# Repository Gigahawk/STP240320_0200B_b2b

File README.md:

# STP240320_0200B_b2b

A PCB that adapts the ribbon connector of the STP240320_0200B_b2b to a [Molex SlimStack 55560-0168](https://www.molex.com/molex/products/part-detail/pcb_headers/0555600168)
> The footprint used is the KiCad native [55560-0161](https://gitlab.com/kicad/libraries/kicad-footprints/-/blob/master/Connector_Molex.pretty/Molex_SlimStack_55560-0161_2x08_P0.50mm_Vertical.kicad_mod), there doesn't seem to be an appreciable difference.

## Background

The STP240320_0200B is a 2.0" 240x320 ST7789 based TFT display.
It is used in many 2.0" ST7789 display modules, some examples:
- [Adafruit 2.0" 320x240 Color IPS TFT Display with microSD Card Breakout](https://www.adafruit.com/product/4311)
- [Waveshare 240×320, General 2inch IPS LCD Display Module](https://www.waveshare.com/2inch-lcd-module.htm)

The display itself can be purchased from [Surenoo Display on AliExpress](https://www.aliexpress.com/item/4000469644849.html), if you find other vendors please feel free to open an issue or PR.

The flex ribbon connector isn't designed to go into a FFC connector, so this board is used to connectorize the display.

### Update 2022-10-27
I have recently purchased more of these displays and they are not the same as the displays I originally purchased back in 2020, nor do they match the picture in the listing.

Original is on the left, the display I recently received on the right:

While I have not tested this new display with the adapter, visually they appear to be functionally identical.
The display housing has the exact same outer dimensions.
The connector has the same number of pins with the same pitch and in the same order.
The connector location relative to the display housing appears to be the same as well

Since I have not tested the display yet with the breakout, I do not know whether:
- The pinout of the connector is actually identical to the original
- The viewing area location matches the original display

## STP240320_0200B_b2b

The `STP240320_0200B_b2b` folder contains KiCad files for the board to board adapter shown above

## STP240320_0200B_b2b_breakout

The `STP240320_0200B_b2b_breakout` folder contains KiCad files for a breakout board similar to the Adafruit breakout with a matching [Molex SlimStack 54722-0164](https://www.molex.com/molex/products/part-detail/pcb_receptacles/0547220164).

## Notes

There appear to be similar displays with SPI interfaces that have FPCs suitable for direct connection into an FFC connector.

The STP240320_0200A sold from the same link above is listed as an 8-bit parallel interface only, but the display looks suspiciously close to some other listings on AliExpress:
- https://www.aliexpress.com/i/1005003204020216.html
- https://www.aliexpress.com/i/2045504893.html

These listings list pins 3 and 4 as `IM1` and `IM2`, which can be used to set the display mode to 8-bit parallel or SPI.

[LCD Wiki](http://www.lcdwiki.com/2.0inch_IPS_Module) documents a breakout board using this display, with a [schematic](http://www.lcdwiki.com/res/MSP2008/2.0IPS_MSP2008_Schematic.pdf) showing the `IMx` pins configuring the display for SPI operation.
The schematic has a link to http://www.qdtft.com, but they don't seem to list this module anymore.

There are a few vendors on AliExpress that appear to be selling this breakout:
- https://www.aliexpress.com/i/1005004116872380.html
- https://www.aliexpress.com/i/1005004116832438.html
- https://www.aliexpress.com/i/32705031396.html
- https://www.aliexpress.com/i/1005004116821841.html

### Update 2022-11-05

I've purchased breakouts from the first link in the above list (XunMing Store), some notes about them:
- They work identically to the STP240320_0200B
    - Tested using Adafruit's [CircuitPython Displayio Quickstart Guide](https://learn.adafruit.com/2-0-inch-320-x-240-color-ips-tft-display/circuitpython-displayio-quickstart)
- The breakout boards use a rather strong foam tape that makes the display hard to separate from the PCB, if possible I recommend purchasing the bare display module on its own for integration into other projects, and to use the breakout only for prototyping
- The display module is significantly larger in all dimensions compared to the STP240320_0200B
    - The bezels are significantly larger, and the whole module is thicker
- The FFC connector used does not save any space compared to the SlimStack connector used.
    - When fully assembled (i.e. B2B adapter connected to the breakout), the SlimStack connectors are about the same height as the closed FFC connector
    - The FFC connector is significantly wider than both the SlimStack connector and the B2B adapter board (perpendicular to the direction of FFC insertion)
    - The FFC connector is about the same length of the B2B adapter board (parallel to the direction of FFC insertion)

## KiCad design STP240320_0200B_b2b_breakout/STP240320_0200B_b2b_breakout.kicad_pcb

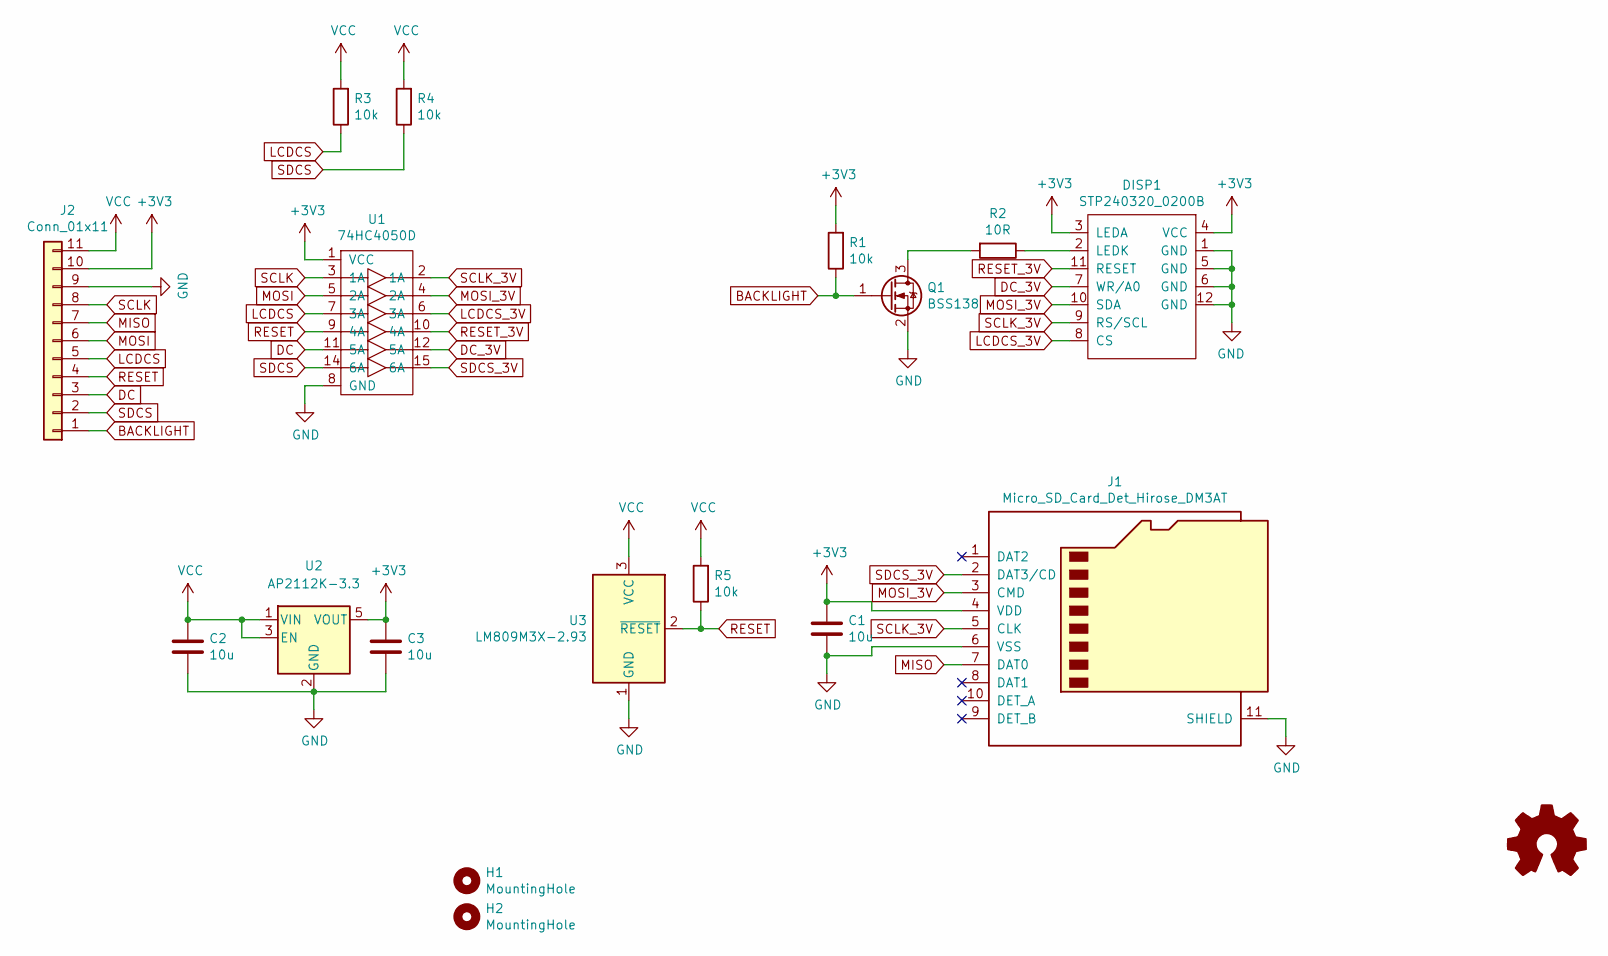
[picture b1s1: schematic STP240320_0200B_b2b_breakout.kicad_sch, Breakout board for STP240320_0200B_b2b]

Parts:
C1, C2, C3: 10u; C_0805_2012Metric_Pad1.18x1.45mm_HandSolder
DISP1: STP240320_0200B; Molex_SlimStack_54722-0164_2x08_P0.50mm_Vertical
H1, H2: MountingHole; MountingHole_2.5mm_Pad
J1: Micro_SD_Card_Det_Hirose_DM3AT; microSD_HC_Hirose_DM3AT-SF-PEJM5
J2: Conn_01x11; PinHeader_1x11_P2.54mm_Vertical
LOGO1: Logo_Open_Hardware_Small; OSHW-Logo2_9.8x8mm_Mask
Q1: BSS138; SOT-23
R1, R3, R4, R5: 10k; R_0805_2012Metric_Pad1.20x1.40mm_HandSolder
R2: 10R; R_0805_2012Metric_Pad1.20x1.40mm_HandSolder
U1: 74HC4050D; SOIC-16_3.9x9.9mm_P1.27mm
U2: AP2112K-3.3; SOT-23-5
U3: LM809M3X-2.93; SOT-23

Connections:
+3V3: C1.1, C3.1, DISP1.3 (LEDA), DISP1.4 (VCC), J1.4 (VDD), J2.10, R1.2, U1.1 (VCC), U2.5 (VOUT)
BACKLIGHT: J2.1, Q1.1 (G), R1.1
DC: J2.3, U1.11 (5A)
DC_3V: DISP1.7 (WR/A0), U1.12 (5A)
GND: C1.2, C2.2, C3.2, DISP1.1 (GND), DISP1.5 (GND), DISP1.6 (GND), DISP1.12 (GND), J1.6 (VSS), J1.11 (SHIELD), J2.9, Q1.2 (S), U1.8 (GND), U2.2 (GND), U3.1 (GND)
LCDCS: J2.5, R3.1, U1.7 (3A)
LCDCS_3V: DISP1.8 (CS), U1.6 (3A)
MISO: J1.7 (DAT0), J2.7
MOSI: J2.6, U1.5 (2A)
MOSI_3V: DISP1.10 (SDA), J1.3 (CMD), U1.4 (2A)
unnamed: DISP1.2 (LEDK), R2.1
unnamed: Q1.3 (D), R2.2
RESET: J2.4, R5.1, U1.9 (4A), U3.2 (~RESET)
RESET_3V: DISP1.11 (RESET), U1.10 (4A)
SCLK: J2.8, U1.3 (1A)
SCLK_3V: DISP1.9 (RS/SCL), J1.5 (CLK), U1.2 (1A)
SDCS: J2.2, R4.1, U1.14 (6A)
SDCS_3V: J1.2 (DAT3/CD), U1.15 (6A)
VCC: C2.1, J2.11, R3.2, R4.2, R5.2, U2.1 (VIN), U2.3 (EN), U3.3 (VCC)

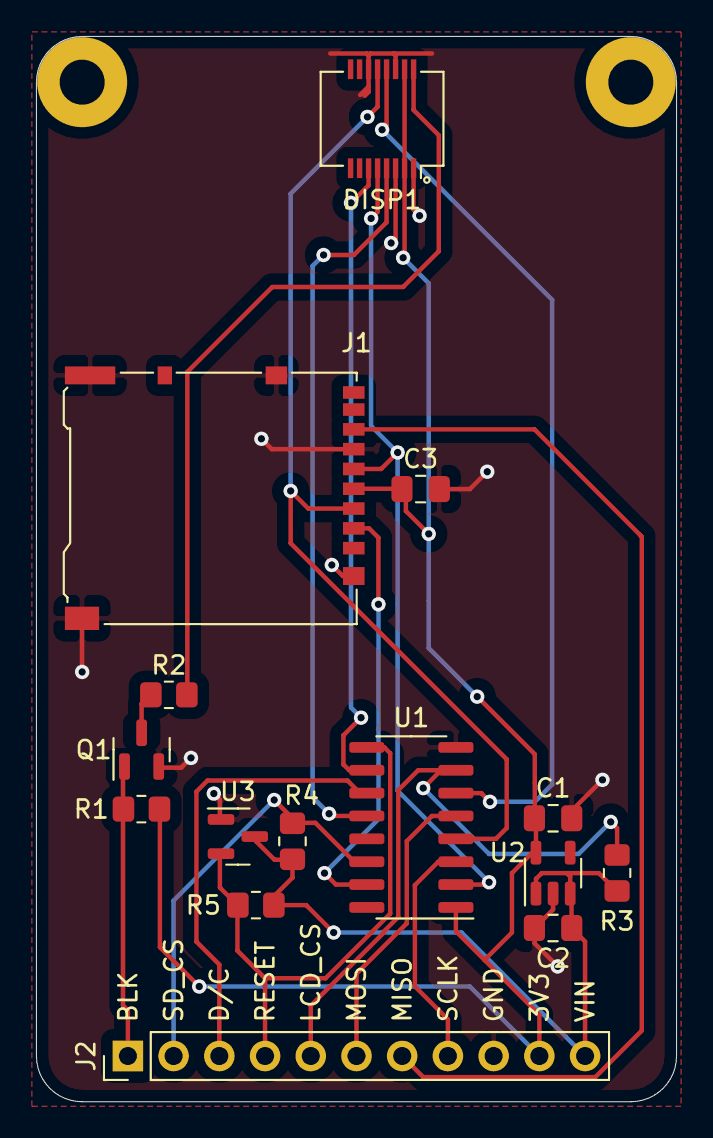
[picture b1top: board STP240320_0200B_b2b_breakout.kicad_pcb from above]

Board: 2 copper layers, 35.6 x 59.2 mm, 18 parts (0 on the bottom side), 19 nets.

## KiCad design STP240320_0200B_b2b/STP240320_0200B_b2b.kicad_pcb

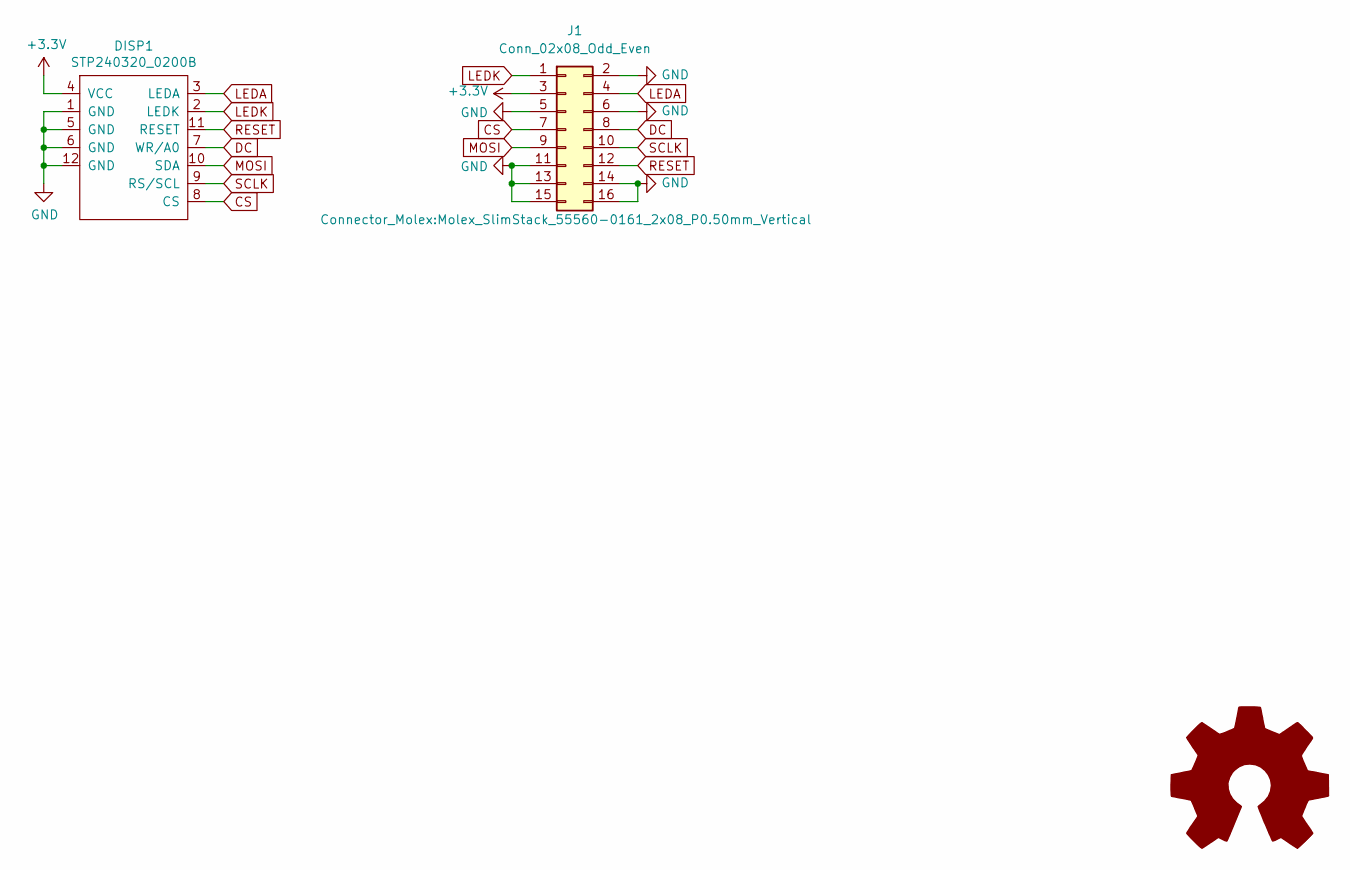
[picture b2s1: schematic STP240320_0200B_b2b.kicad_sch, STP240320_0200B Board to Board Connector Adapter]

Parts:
DISP1: STP240320_0200B
J1: Conn_02x08_Odd_Even; Molex_SlimStack_55560-0161_2x08_P0.50mm_Vertical
SYM1: Logo_Open_Hardware_Large; OSHW-Logo2_1.3x1.3mm_Mask

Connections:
+3V3: DISP1.4 (VCC), J1.3
CS: DISP1.8 (CS), J1.7
DC: DISP1.7 (WR/A0), J1.8
GND: DISP1.1 (GND), DISP1.5 (GND), DISP1.6 (GND), DISP1.12 (GND), J1.2, J1.5, J1.6, J1.11, J1.13, J1.14, J1.15, J1.16
LEDA: DISP1.3 (LEDA), J1.4
LEDK: DISP1.2 (LEDK), J1.1
MOSI: DISP1.10 (SDA), J1.9
RESET: DISP1.11 (RESET), J1.12
SCLK: DISP1.9 (RS/SCL), J1.10

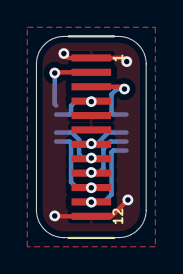
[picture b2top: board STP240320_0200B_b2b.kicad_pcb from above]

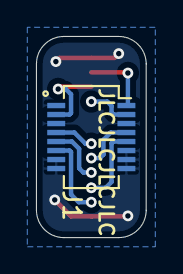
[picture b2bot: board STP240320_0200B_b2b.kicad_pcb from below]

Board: 2 copper layers, 6.1 x 11.2 mm, 3 parts (2 on the bottom side), 9 nets.

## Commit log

2020-11-27 Create display to molex slimstack 55560 plug
2020-11-27 Reverse board to board connector pinout.
    Display symbol can now be used directly with 54722 parts.
2020-11-27 Create breakout for board to board adapter
2020-12-15 Fix library paths
2022-09-24 kicad: update to kicad 6
2022-09-24 ci: add CI
2022-09-24 ci: add CI (#1)
2022-09-26 ci: add release support
2022-09-26 ci: add release support (#2)
2022-09-26 Revert "ci: add release support (#2)"
    This reverts commit f3a1c30362bc760beaf5669eca90d55fbc6df8b2.
2022-09-26 bugfix: skip act check for release job
2022-09-26 bugfix: skip act check for release job (#4)
2022-09-27 b2b: default thickness is 0.8mm
2022-10-14 readme: add readme
2022-10-27 readme: document new display version from vendor
2022-11-06 readme: document display with ffc connector
2023-10-04 ci: update to kicad 7
2023-10-04 all: update projects to kicad 7
2023-10-04 all: cleanup revision info
2023-10-04 ci: fix boardview export
2023-10-04 b2b: fix broken tag text
2023-10-04 breakout: add date to silkscreen
